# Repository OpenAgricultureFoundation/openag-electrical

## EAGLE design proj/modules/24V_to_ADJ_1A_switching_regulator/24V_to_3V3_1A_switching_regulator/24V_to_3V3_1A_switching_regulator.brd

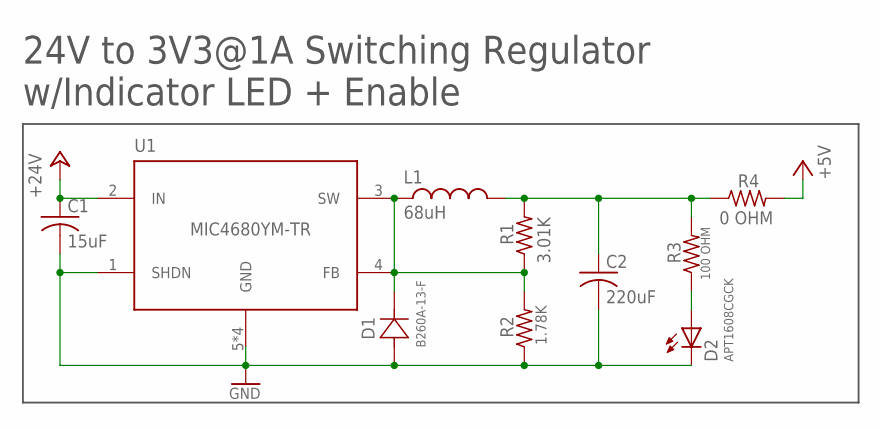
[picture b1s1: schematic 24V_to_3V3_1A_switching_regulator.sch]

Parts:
C1: 15uF; CT7343
C2: 220uF; CT7343
D1: B260A-13-F; SMA
D2: APT1608CGCK; CHIPLED_0603
L1: 68uH; UP2B
R1: 3.01K; RC0603N
R2: 1.78K; RC0603N
R3: 100 OHM; RC0603N
R4: 0 OHM; RC0603N
U1: MIC4680YM-TR; SOIC8

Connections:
+5V: R4.2
+24V: C1.+ (1(+)), U1.2 (IN)
GND: C1.- (2(-)), C2.- (2(-)), D1.2 (21), D2.C, R2.1, U1.1 (SHDN), U1.5 (GND), U1.6 (GND), U1.7 (GND), U1.8 (GND)
unnamed: D2.A, R3.1
unnamed: C2.+ (1(+)), L1.2, R1.2, R3.2, R4.1
unnamed: D1.1 (12), L1.1, R1.1, R2.2, U1.3 (SW), U1.4 (FB)

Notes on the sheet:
24V to 3V3@1A Switching Regulator w/Indicator LED + Enable

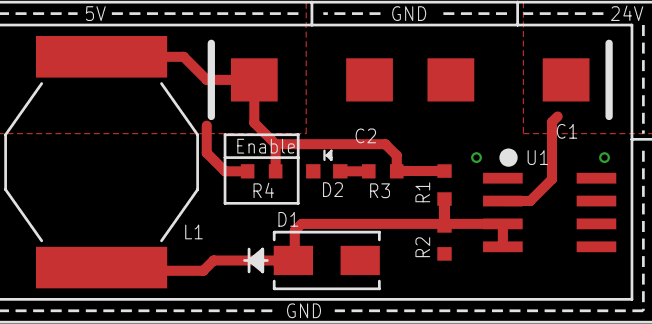
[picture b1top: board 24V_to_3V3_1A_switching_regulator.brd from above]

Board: 2 copper layers, 10 parts (0 on the bottom side), 5 nets.

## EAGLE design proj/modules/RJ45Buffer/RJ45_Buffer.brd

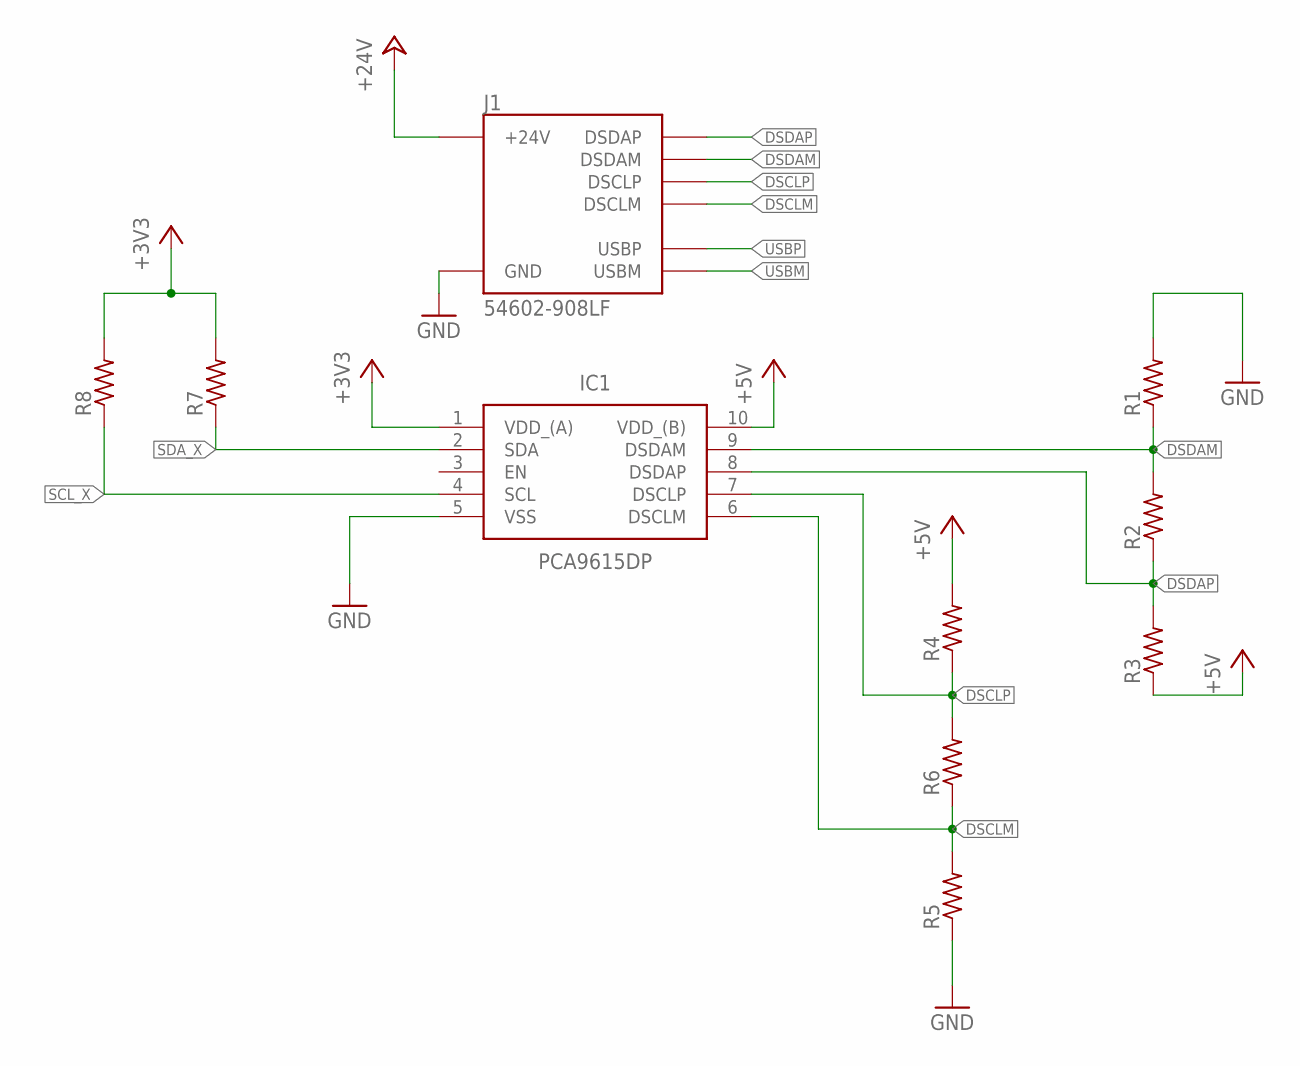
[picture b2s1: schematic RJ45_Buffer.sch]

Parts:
IC1: PCA9615DP; SOP50P490X110-10N
J1: 54602-908LF; OPENAG-V1-RJ45
R1, R2, R3, R4, R5, R6, R7, R8: R-US_R0603; R0603

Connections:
+3V3: IC1.1 (VDD_(A)), R7.2, R8.2
+5V: IC1.10 (VDD_(B)), R3.1, R4.2
+24V: J1.24V(6) (+24V)
DSCLM: IC1.6 (DSCLM), J1.DSCLM(5) (DSCLM), R5.2, R6.1
DSCLP: IC1.7 (DSCLP), J1.DSCLP(4) (DSCLP), R4.1, R6.2
DSDAM: IC1.9 (DSDAM), J1.DSDAM(2) (DSDAM), R1.1, R2.2
DSDAP: IC1.8 (DSDAP), J1.DSDAP(1) (DSDAP), R2.1, R3.2
GND: IC1.5 (VSS), J1.GND(3) (GND), R1.2, R5.1
SCL_X: IC1.4 (SCL), R8.1
SDA_X: IC1.2 (SDA), R7.1
USBM: J1.USBM(8) (USBM)
USBP: J1.USBP(7) (USBP)

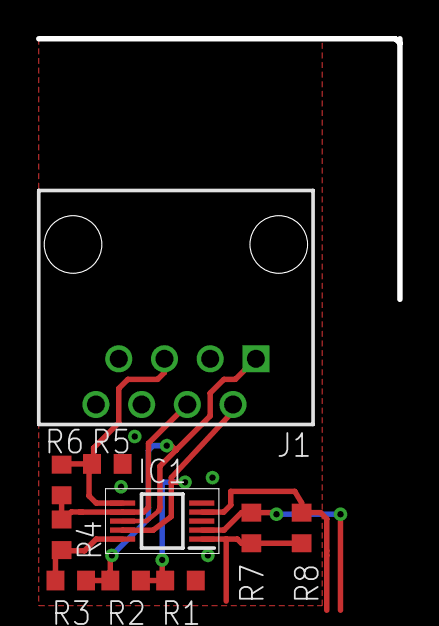
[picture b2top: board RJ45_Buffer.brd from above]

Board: 2 copper layers, 10 parts (0 on the bottom side), 9 nets.

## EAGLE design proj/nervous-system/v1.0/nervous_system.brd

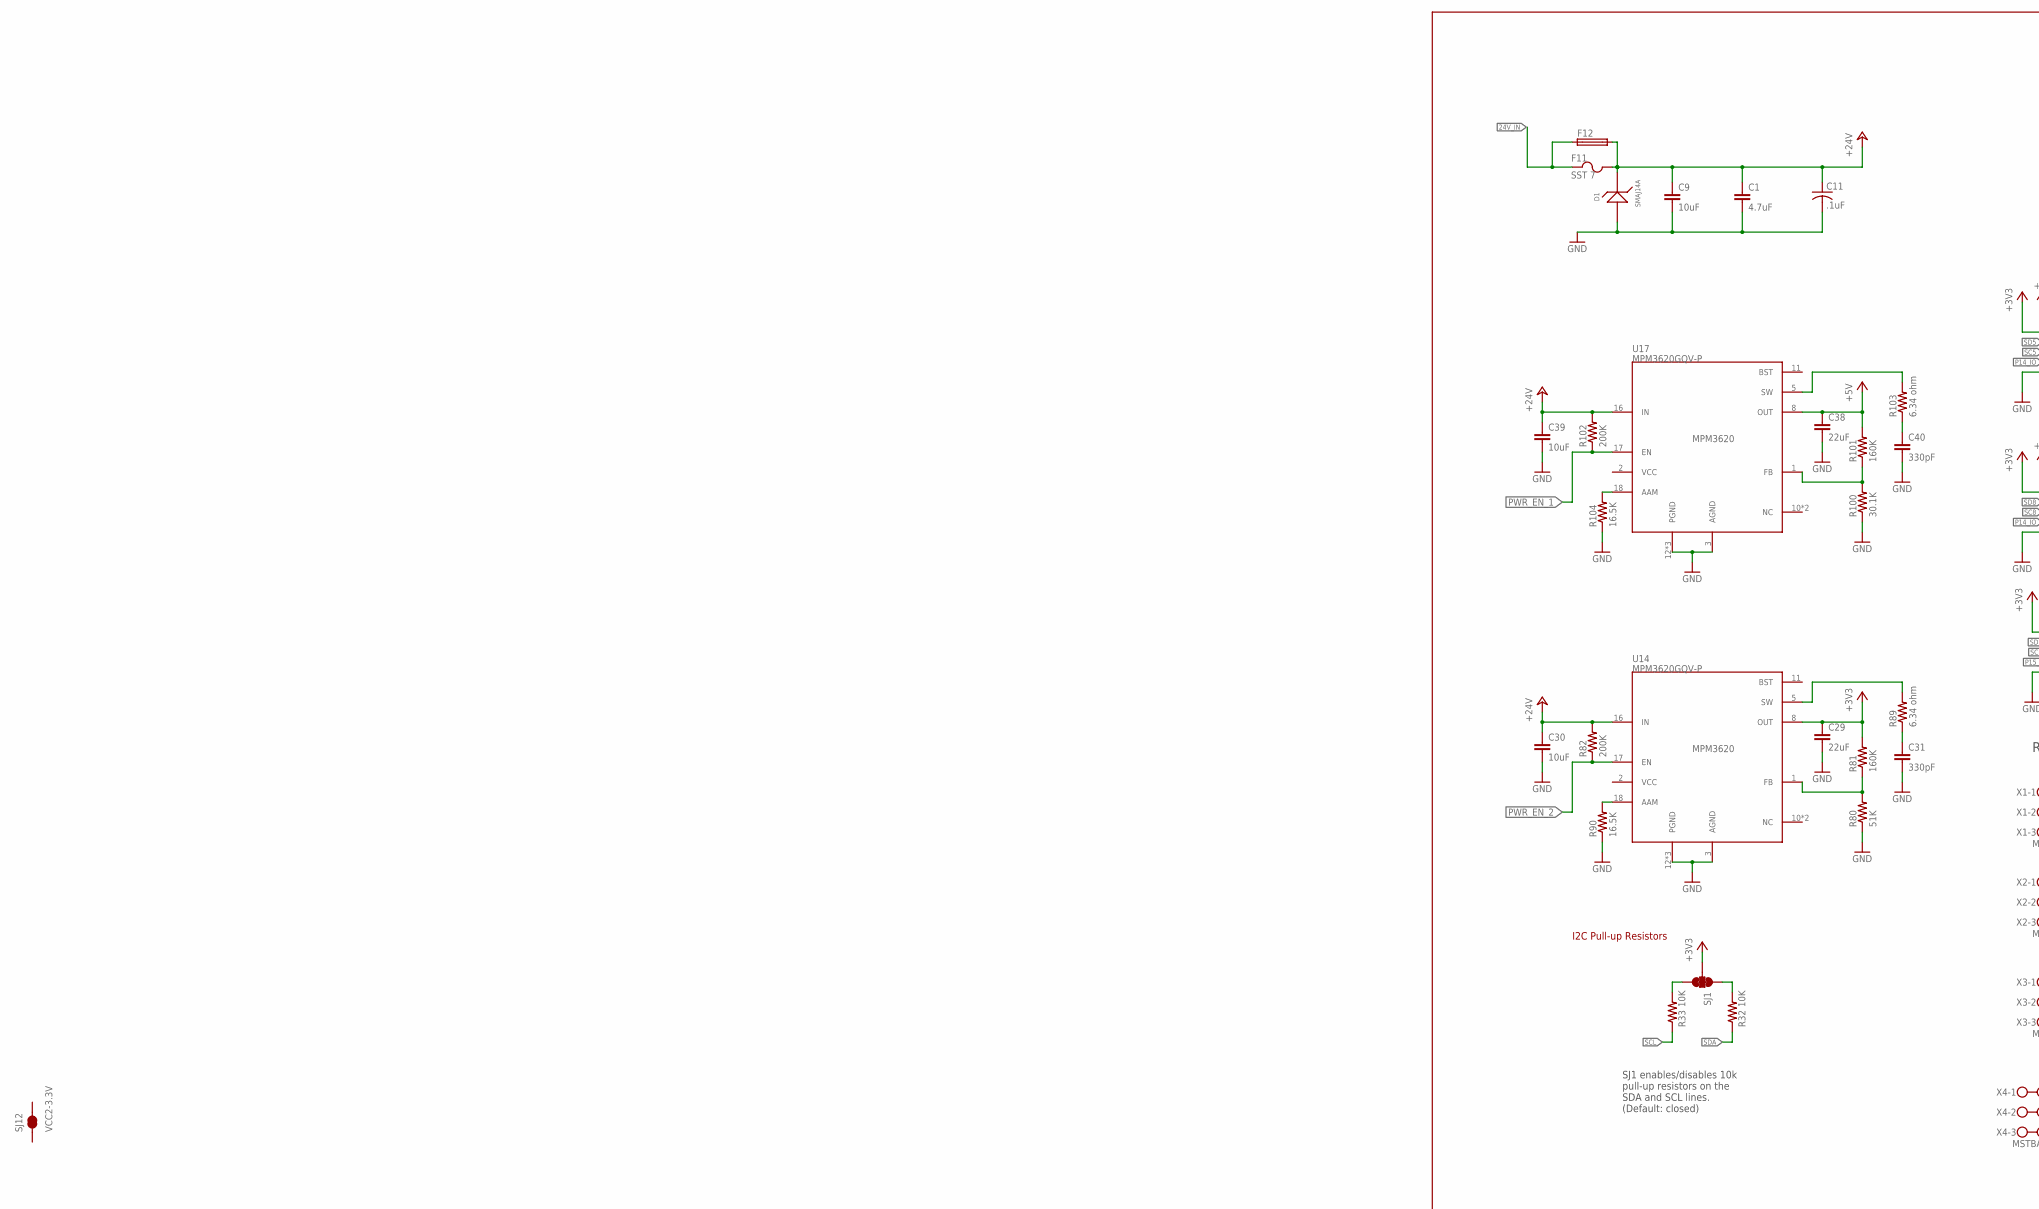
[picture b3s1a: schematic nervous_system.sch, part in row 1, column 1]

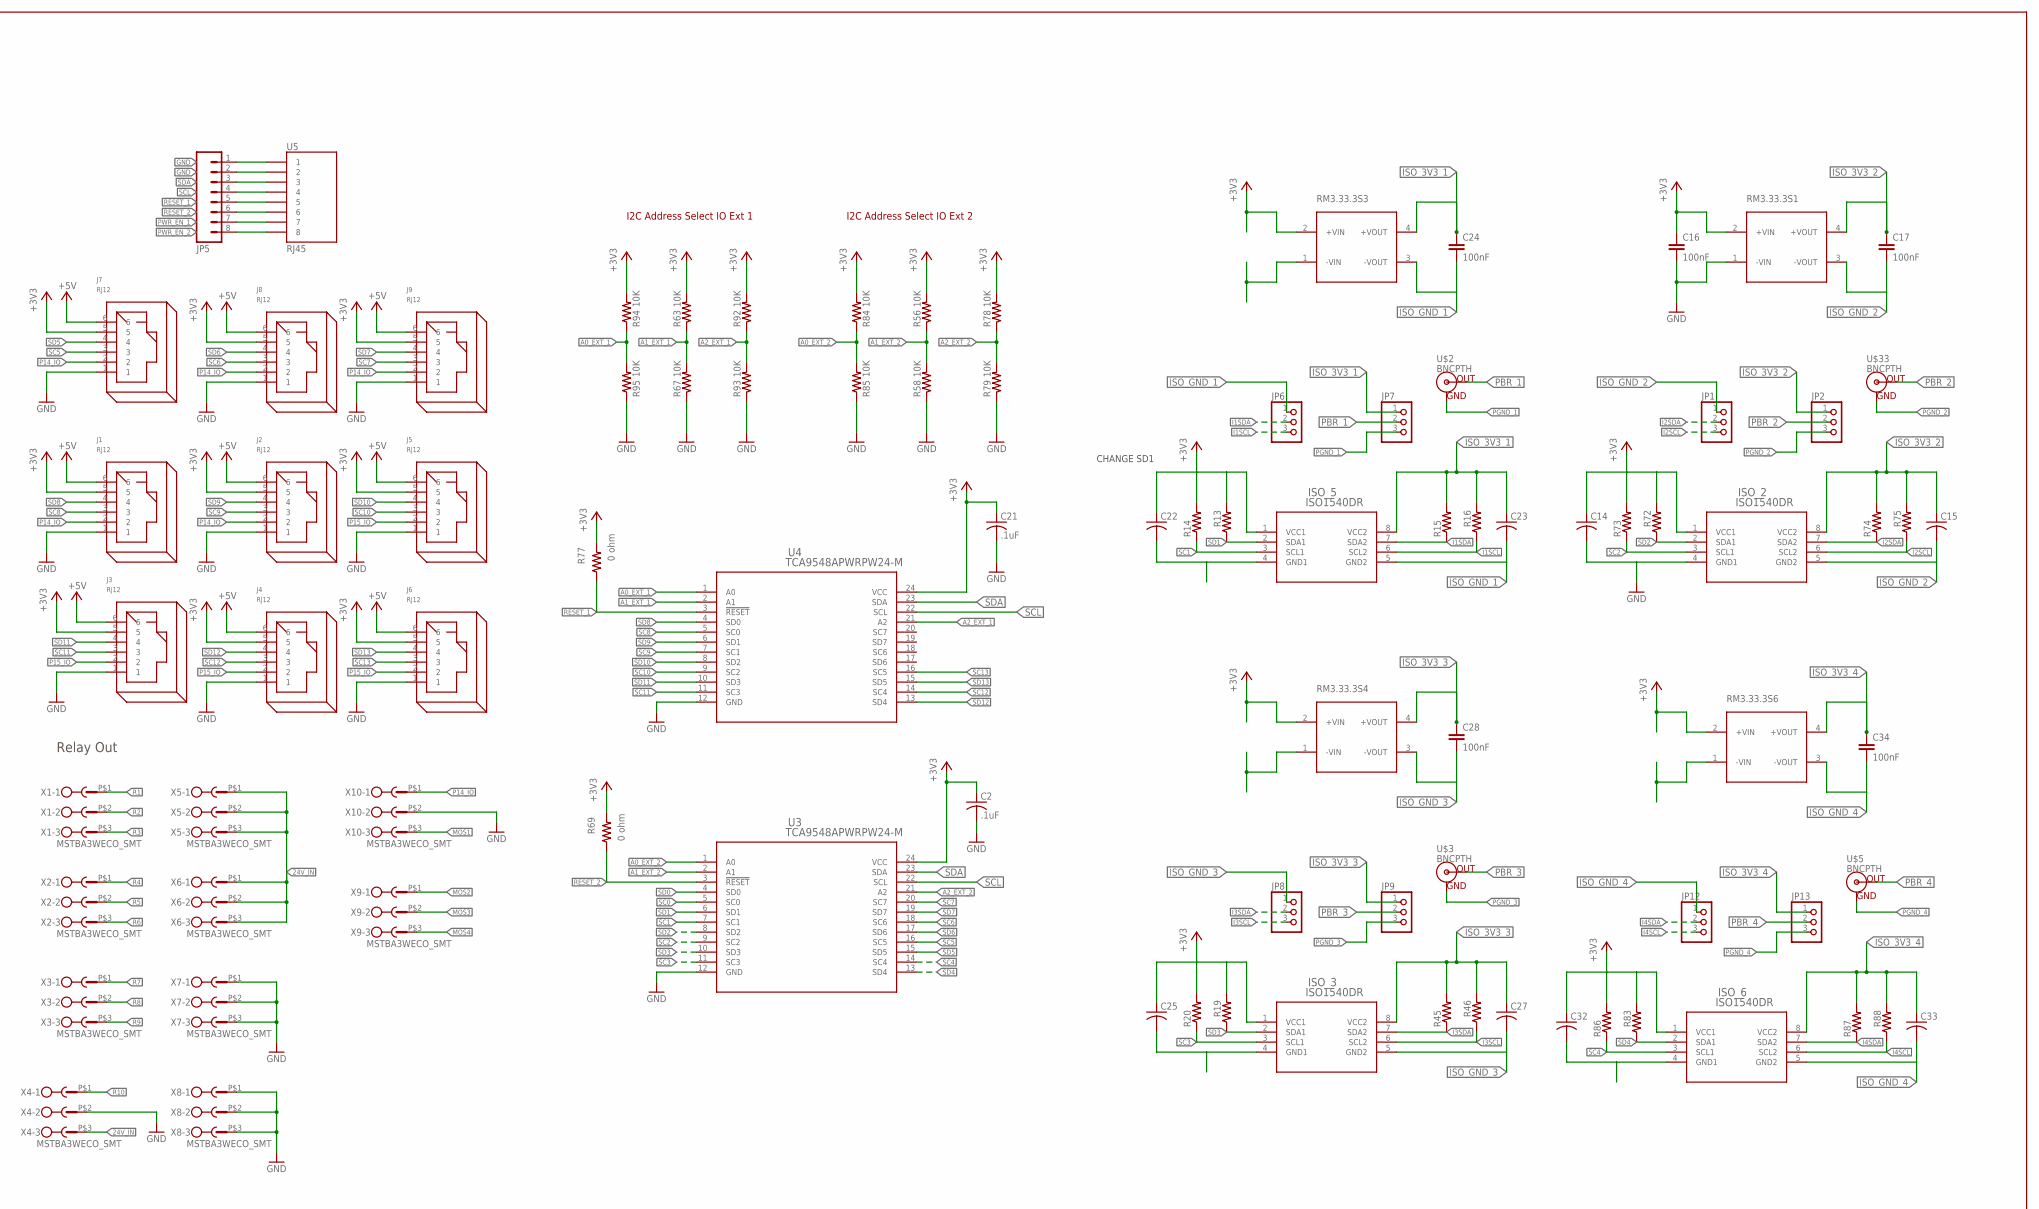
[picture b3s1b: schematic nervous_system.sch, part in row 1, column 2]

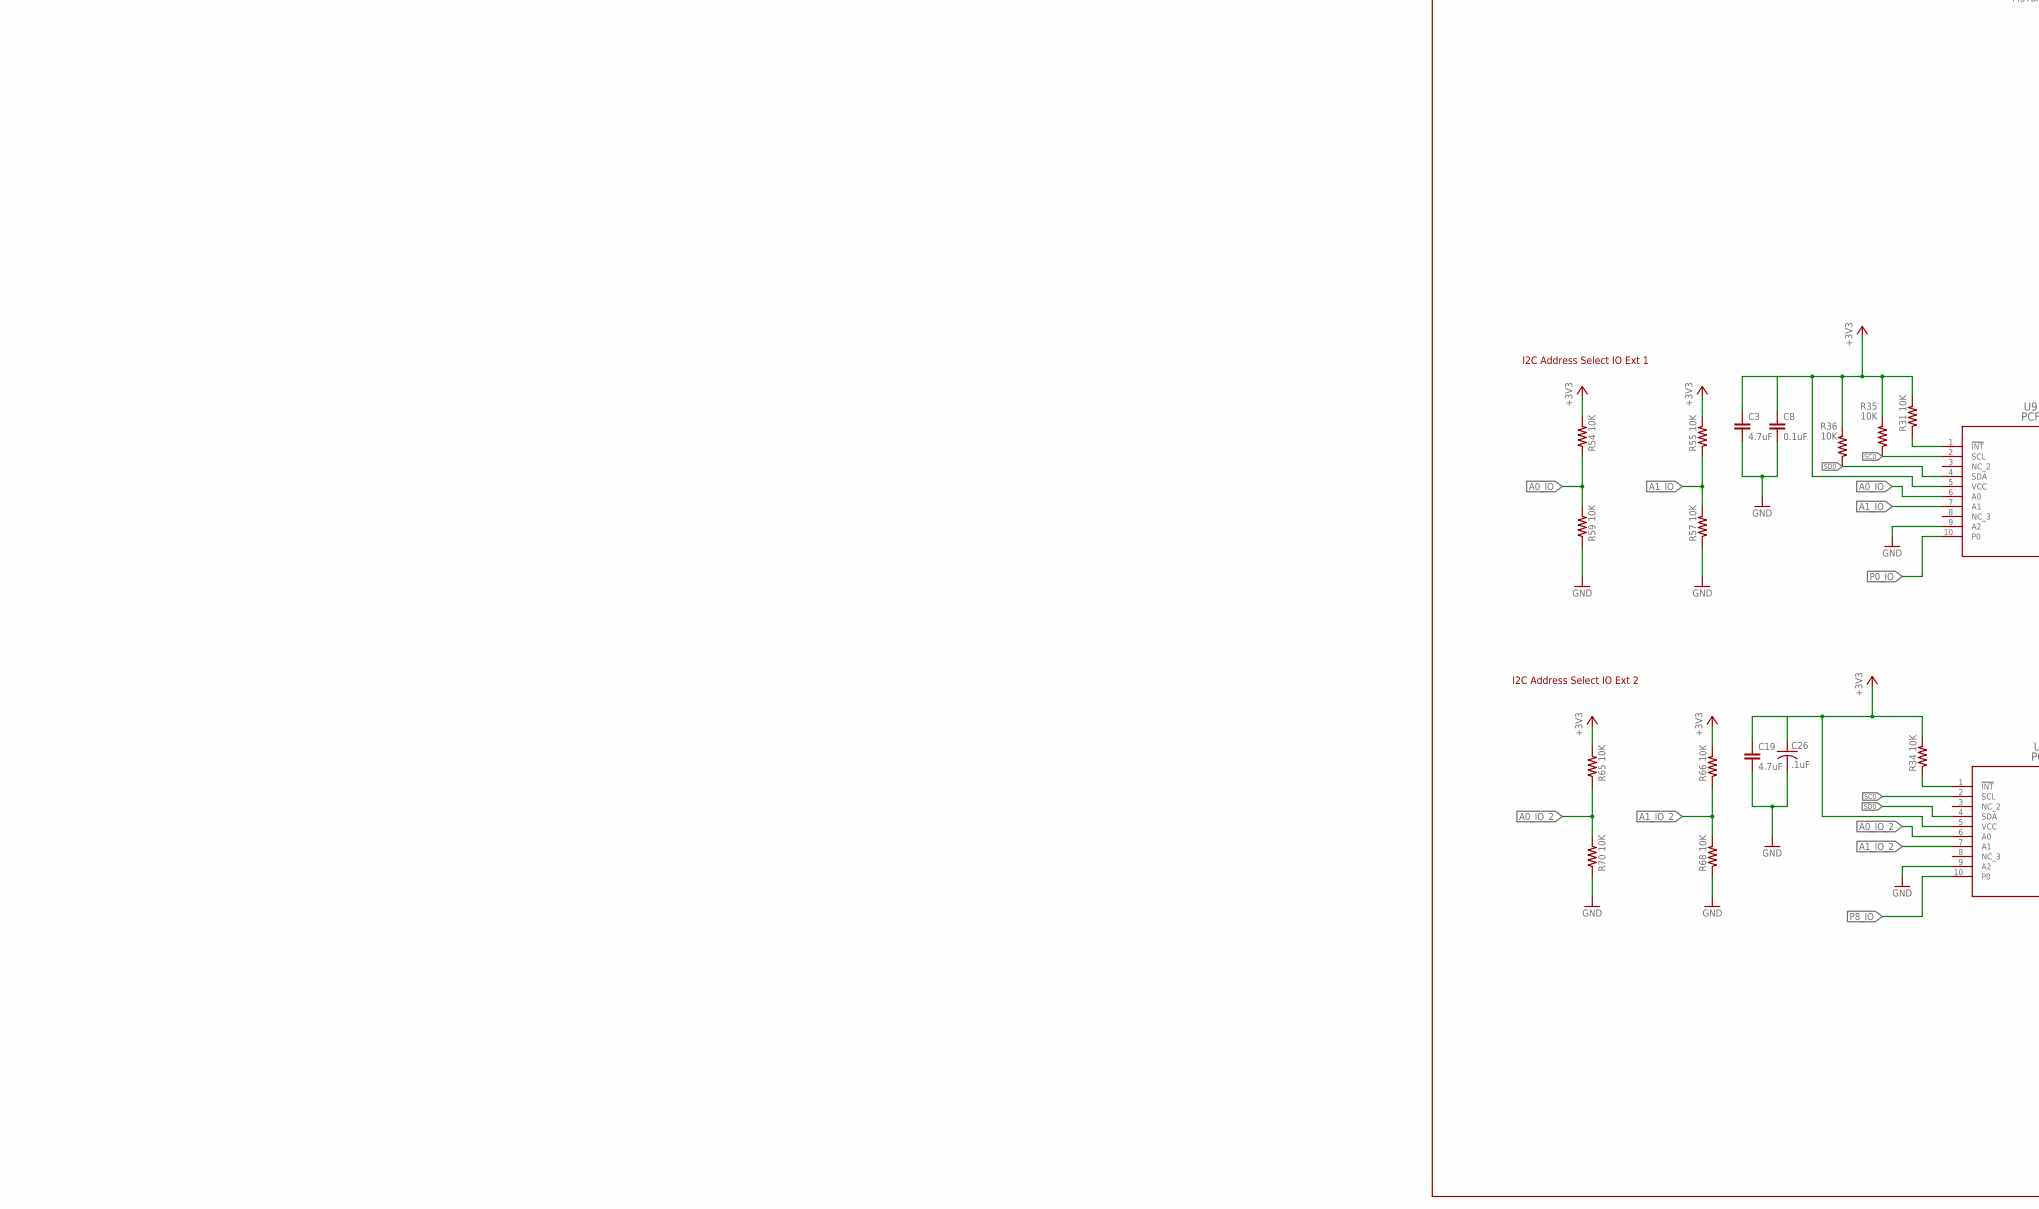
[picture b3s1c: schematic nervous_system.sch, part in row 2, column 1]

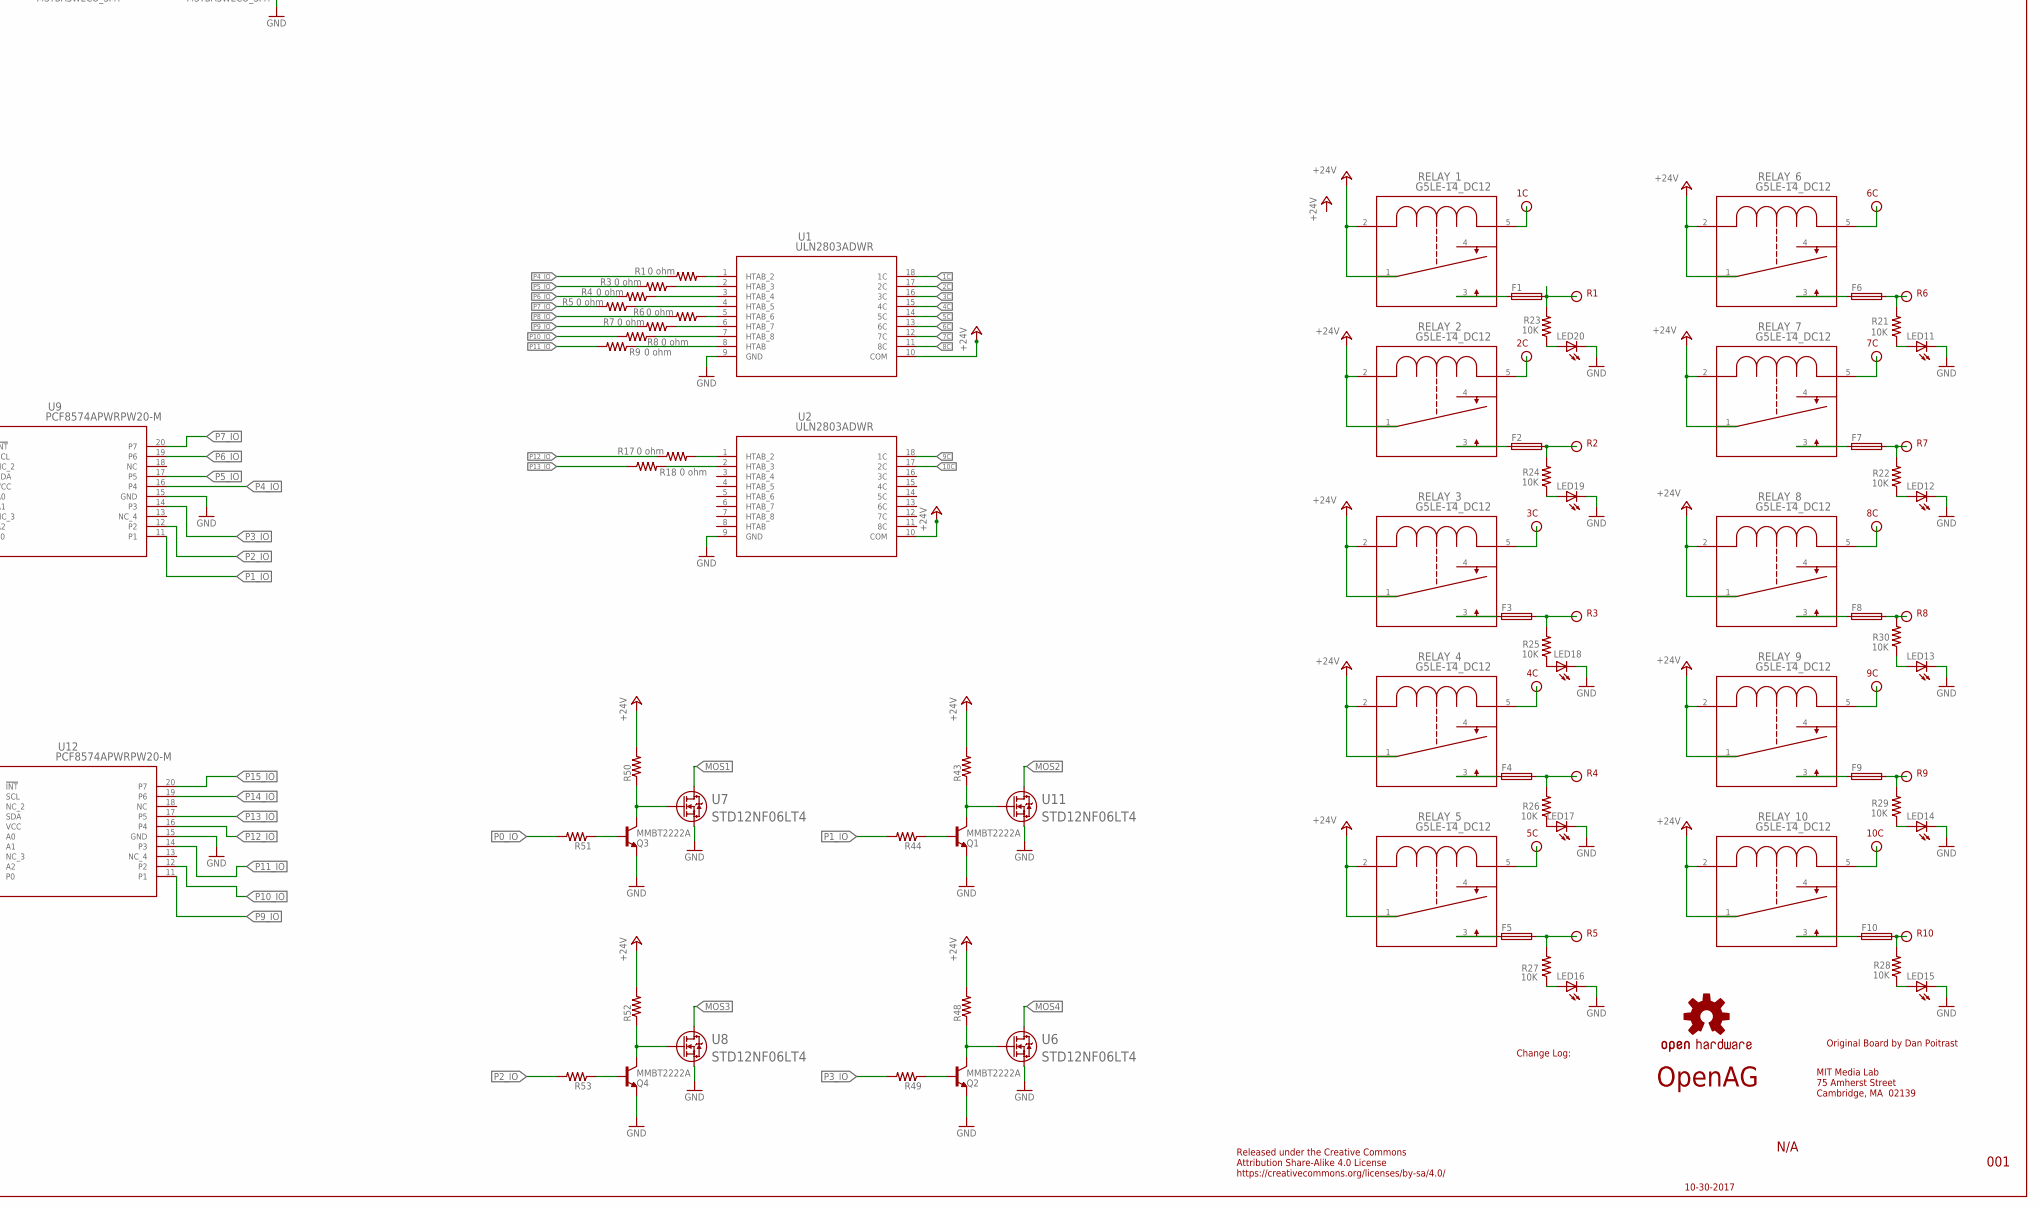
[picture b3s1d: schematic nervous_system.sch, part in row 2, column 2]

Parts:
C1, C3, C19: 4.7uF; CAP_C1206
C2, C11, C21, C26: .1uF; C0603@1
C8: 0.1uF; C1206C
C9, C30, C39: 10uF; C1206
C14, C15, C22, C23, C25, C27, C32, C33: C-USC0603; C0603@1
C16, C17, C24, C28, C34: 100nF; 0805@1
C29, C38: 22uF; C1206
C31, C40: 330pF; C0603
D1: SMAJ14A; DO-214AC
F1, F2, F3, F4, F5, F6, F7, F8, F9, F10, F12: GSH15
F11: SST 7; SS
ISO_2, ISO_3, ISO_5, ISO_6: ISO1540DR; D8
J1, J2, J3, J4, J5, J6, J7, J8, J9: RJ12
JP1, JP2, JP6, JP7, JP8, JP9, JP12, JP13: PINHD-1X3; 1X03
JP5: M08; 1X08
LED11, LED12, LED13, LED14, LED15, LED16, LED17, LED18, LED19, LED20: LED; SMARTLED-TTW
LOGO3: OSHW-LOGOS; OSHW-LOGO-S
Q1, Q2, Q3, Q4: MMBT2222A; SOT23-BEC
R1, R3, R4, R5, R6, R7, R8, R9, R17, R18, R69, R77: 0 ohm; R0603
R13, R14, R15, R16, R19, R20, R45, R46, R72, R73, R74, R75, R83, R86, R87, R88: R-US_R0603; R0603
R21, R22, R23, R24, R25, R26, R27, R28, R29, R30: 10K; R0603
R31, R32, R33, R34, R35, R36, R54, R55, R56, R57, R58, R59, R63, R65, R66, R67, R68, R70, R78, R79, R84, R85, R92, R93, R94, R95: 10K; 0603-RES
R43, R44, R48, R49, R50, R51, R52, R53: R-US_R0805W; R0805W
R80: 51K; RC0603N
R81, R101: 160K; RC0603N
R82, R102: 200K; RC0603N
R89, R103: 6.34 ohm; R0805
R90, R104: 16.5K; RC0603N
R100: 30.1K; RC0603N
RELAY_1, RELAY_2, RELAY_3, RELAY_4, RELAY_5, RELAY_6, RELAY_7, RELAY_8, RELAY_9, RELAY_10: G5LE-14_DC12; RELAY_G5LE-1
RM3.33.3S1, RM3.33.3S3, RM3.33.3S4, RM3.33.3S6: ROE-0505S; SIP4
SJ1: JUMPER-PAD-3-NC_BY_TRACE; PAD-JUMPER-3-3OF3_NC_BY_TRACE_YES_SILK_FULL_BOX
SJ12: VCC2-3.3V; PAD-JUMPER-2-NC_BY_TRACE_YES_SILK
U1, U2: ULN2803ADWR; DW18
U3, U4: TCA9548APWRPW24-M; PW24-M
U5: RJ45; RJ45-8
U6, U7, U8, U11: STD12NF06LT4; DPAK
U9, U12: PCF8574APWRPW20-M; PW20-M
U14, U17: MPM3620GQV-P; 20-POWERLFQFN-MODULE
U$2, U$3, U$5, U$33: BNCPTH; BNC
X1, X2, X3, X4, X5, X6, X7, X8, X9, X10: MSTBA3WECO_SMT; WECO_3POS_SMT

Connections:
1C: RELAY_1.5, U1.18 (1C)
2C: RELAY_2.5, U1.17 (2C)
3C: RELAY_3.5, U1.16 (3C)
4C: RELAY_4.5, U1.15 (4C)
5C: RELAY_5.5, U1.14 (5C)
6C: RELAY_6.5, U1.13 (6C)
7C: RELAY_7.5, U1.12 (7C)
8C: RELAY_8.5, U1.11 (8C)
9C: RELAY_9.5, U2.18 (1C)
10C: RELAY_10.5, U2.17 (2C)
24V_IN: F11.1, F12.1, X4.P$3, X5.P$1, X5.P$2, X5.P$3, X6.P$1, X6.P$2, X6.P$3
+3V3: C2.1, C3.1, C8.1, C14.1, C16.1, C19.1, C21.1, C22.1, C25.1, C26.1, C29.1, C32.1, ISO_2.1 (VCC1), ISO_3.1 (VCC1), ISO_5.1 (VCC1), ISO_6.1 (VCC1), J1.5, J2.5, J3.5, J4.5, J5.5, J6.5, J7.5, J8.5, J9.5, R13.2, R14.2, R19.2, R20.2, R31.2, R34.2, R35.2, R36.2, R54.2, R55.2, R56.2, R63.2, R65.2, R66.2, R69.2, R72.2, R73.2, R77.2, R78.2, R81.2, R83.2, R84.2, R86.2, R92.2, R94.2, RM3.33.3S1.2 (+VIN), RM3.33.3S3.2 (+VIN), RM3.33.3S4.2 (+VIN), RM3.33.3S6.2 (+VIN), SJ1.2, U3.24 (VCC), U4.24 (VCC), U9.5 (VCC), U12.5 (VCC), U14.8 (OUT)
+5V: C38.1, J1.6, J2.6, J3.6, J4.6, J5.6, J6.6, J7.6, J8.6, J9.6, R101.2, U17.8 (OUT)
+24V: C1.1, C9.1, C11.1, C30.1, C39.1, D1.C, F11.2, F12.2, R43.2, R48.2, R50.2, R52.2, R82.2, R102.2, RELAY_1.1 (2), RELAY_1.2 (1), RELAY_2.1 (2), RELAY_2.2 (1), RELAY_3.1 (2), RELAY_3.2 (1), RELAY_4.1 (2), RELAY_4.2 (1), RELAY_5.1 (2), RELAY_5.2 (1), RELAY_6.1 (2), RELAY_6.2 (1), RELAY_7.1 (2), RELAY_7.2 (1), RELAY_8.1 (2), RELAY_8.2 (1), RELAY_9.1 (2), RELAY_9.2 (1), RELAY_10.1 (2), RELAY_10.2 (1), U1.10 (COM), U2.10 (COM), U14.16 (IN), U17.16 (IN)
A0_EXT_1: R94.1, R95.2, U4.1 (A0)
A0_EXT_2: R84.1, R85.2, U3.1 (A0)
A0_IO: R54.1, R59.2, U9.6 (A0)
A0_IO_2: R65.1, R70.2, U12.6 (A0)
A1_EXT_1: R63.1, R67.2, U4.2 (A1)
A1_EXT_2: R56.1, R58.2, U3.2 (A1)
A1_IO: R55.1, R57.2, U9.7 (A1)
A1_IO_2: R66.1, R68.2, U12.7 (A1)
A2_EXT_1: R92.1, R93.2, U4.21 (A2)
A2_EXT_2: R78.1, R79.2, U3.21 (A2)
GND: C1.2, C2.2, C3.2, C8.2, C9.2, C11.2, C14.2, C16.2, C19.2, C21.2, C22.2, C25.2, C26.2, C29.2, C30.2, C31.2, C32.2, C38.2, C39.2, C40.2, D1.A, ISO_2.4 (GND1), ISO_3.4 (GND1), ISO_5.4 (GND1), ISO_6.4 (GND1), J1.1, J2.1, J3.1, J4.1, J5.1, J6.1, J7.1, J8.1, J9.1, JP5.1, JP5.2, LED11.C@1 (C), LED12.C@1 (C), LED13.C@1 (C), LED14.C@1 (C), LED15.C@1 (C), LED16.C@1 (C), LED17.C@1 (C), LED18.C@1 (C), LED19.C@1 (C), LED20.C@1 (C), Q1.E, Q2.E, Q3.E, Q4.E, R57.1, R58.1, R59.1, R67.1, R68.1, R70.1, R79.1, R80.1, R85.1, R90.1, R93.1, R95.1, R100.1, R104.1, RM3.33.3S1.1 (-VIN), RM3.33.3S3.1 (-VIN), RM3.33.3S4.1 (-VIN), RM3.33.3S6.1 (-VIN), U1.9 (GND), U2.9 (GND), U3.12 (GND), U4.12 (GND), U5.1, U5.2, U6.2 (3), U7.2 (3), U8.2 (3), U9.9 (A2), U9.15 (GND), U11.2 (3), U12.9 (A2), U12.15 (GND), U14.3 (AGND), U14.12 (PGND), U14.13 (PGND), U14.14 (PGND), U17.3 (AGND), U17.12 (PGND), U17.13 (PGND), U17.14 (PGND), X4.P$2, X7.P$1, X7.P$2, X7.P$3, X8.P$1, X8.P$2, X8.P$3, X10.P$2
HTAB: U2.8 (HTAB)
HTAB_4: U2.3 (HTAB_4)
HTAB_5: U2.4 (HTAB_5)
HTAB_6: U2.5 (HTAB_6)
HTAB_7: U2.6 (HTAB_7)
HTAB_8: U2.7 (HTAB_8)
I1SCL: ISO_5.6 (SCL2), JP6.3, R16.1
I1SDA: ISO_5.7 (SDA2), JP6.2, R15.1
I2SCL: ISO_2.6 (SCL2), JP1.3, R75.1
I2SDA: ISO_2.7 (SDA2), JP1.2, R74.1
I3SCL: ISO_3.6 (SCL2), JP8.3, R46.1
I3SDA: ISO_3.7 (SDA2), JP8.2, R45.1
I4SCL: ISO_6.6 (SCL2), JP12.3, R88.1
I4SDA: ISO_6.7 (SDA2), JP12.2, R87.1
ISO_3V3_1: C23.1, C24.1, ISO_5.8 (VCC2), JP7.1, R15.2, R16.2, RM3.33.3S3.4 (+VOUT)
ISO_3V3_2: C15.1, C17.1, ISO_2.8 (VCC2), JP2.1, R74.2, R75.2, RM3.33.3S1.4 (+VOUT)
ISO_3V3_3: C27.1, C28.1, ISO_3.8 (VCC2), JP9.1, R45.2, R46.2, RM3.33.3S4.4 (+VOUT)
ISO_3V3_4: C33.1, C34.1, ISO_6.8 (VCC2), JP13.1, R87.2, R88.2, RM3.33.3S6.4 (+VOUT)
ISO_GND_1: C23.2, C24.2, ISO_5.5 (GND2), JP6.1, RM3.33.3S3.3 (-VOUT)
ISO_GND_2: C15.2, C17.2, ISO_2.5 (GND2), JP1.1, RM3.33.3S1.3 (-VOUT)
ISO_GND_3: C27.2, C28.2, ISO_3.5 (GND2), JP8.1, RM3.33.3S4.3 (-VOUT)
ISO_GND_4: C33.2, C34.2, ISO_6.5 (GND2), JP12.1, RM3.33.3S6.3 (-VOUT)
MOS1: U7.3 (2), X10.P$3
MOS2: U11.3 (2), X9.P$1
MOS3: U8.3 (2), X9.P$2
MOS4: U6.3 (2), X9.P$3
unnamed: R1.2, U1.1 (HTAB_2)
unnamed: R3.1, U1.2 (HTAB_3)
unnamed: R4.1, U1.3 (HTAB_4)
unnamed: R5.1, U1.4 (HTAB_5)
unnamed: R6.1, U1.5 (HTAB_6)
unnamed: R7.1, U1.6 (HTAB_7)
unnamed: R8.1, U1.7 (HTAB_8)
unnamed: R9.1, U1.8 (HTAB)
unnamed: F10.1, RELAY_10.3
unnamed: F9.1, RELAY_9.3
unnamed: F8.1, RELAY_8.3
unnamed: F7.1, RELAY_7.3
unnamed: R80.2, R81.1, U14.1 (FB)
unnamed: R89.2, U14.5 (SW)
unnamed: C31.1, R89.1
unnamed: R90.2, U14.18 (AAM)
unnamed: F6.1, RELAY_6.3
unnamed: F1.1, RELAY_1.3
unnamed: F2.1, RELAY_2.3
unnamed: F3.1, RELAY_3.3
unnamed: F4.1, RELAY_4.3
unnamed: R100.2, R101.1, U17.1 (FB)
unnamed: F5.1, RELAY_5.3
unnamed: R103.2, U17.5 (SW)
unnamed: Q1.C, R43.1, U11.1
unnamed: Q1.B, R44.1
unnamed: C40.1, R103.1
unnamed: R104.2, U17.18 (AAM)
unnamed: Q2.C, R48.1, U6.1
unnamed: Q2.B, R49.1
unnamed: Q3.C, R50.1, U7.1
unnamed: Q3.B, R51.1
unnamed: R17.2, U2.1 (HTAB_2)
unnamed: R18.2, U2.2 (HTAB_3)
unnamed: R34.1, U12.1 (!INT)
unnamed: LED11.A@1 (A), R21.1
unnamed: LED12.A@1 (A), R22.1
unnamed: LED16.A@1 (A), R27.1
unnamed: LED17.A@1 (A), R26.1
unnamed: LED18.A@1 (A), R25.1
unnamed: LED20.A@1 (A), R23.1
unnamed: LED19.A@1 (A), R24.1
unnamed: LED13.A@1 (A), R30.1
unnamed: LED14.A@1 (A), R29.1
unnamed: LED15.A@1 (A), R28.1
unnamed: Q4.C, R52.1, U8.1
unnamed: Q4.B, R53.1
unnamed: R31.1, U9.1 (!INT)
unnamed: R33.2, SJ1.3
unnamed: R32.2, SJ1.1
P0_IO: R51.2, U9.10 (P0)
P1_IO: R44.2, U9.11 (P1)
P2_IO: R53.2, U9.12 (P2)
P3_IO: R49.2, U9.14 (P3)
P4_IO: R1.1, U9.16 (P4)
P5_IO: R3.2, U9.17 (P5)
P6_IO: R4.2, U9.19 (P6)
P7_IO: R5.2, U9.20 (P7)
P8_IO: R6.2, U12.10 (P0)
P9_IO: R7.2, U12.11 (P1)
P10_IO: R8.2, U12.12 (P2)
P11_IO: R9.2, U12.14 (P3)
P12_IO: R17.1, U12.16 (P4)
P13_IO: R18.1, U12.17 (P5)
P14_IO: J1.2, J2.2, J7.2, J8.2, J9.2, U12.19 (P6), X10.P$1
P15_IO: J3.2, J4.2, J5.2, J6.2, U12.20 (P7)
PBR_1: JP7.2, U$2.S (OUT)
PBR_2: JP2.2, U$33.S (OUT)
PBR_3: JP9.2, U$3.S (OUT)
PBR_4: JP13.2, U$5.S (OUT)
PGND_1: JP7.3, U$2.GND
PGND_2: JP2.3, U$33.GND
PGND_3: JP9.3, U$3.GND
PGND_4: JP13.3, U$5.GND
PWR_EN_1: JP5.7, R102.1, U5.7, U17.17 (EN)
PWR_EN_2: JP5.8, R82.1, U5.8, U14.17 (EN)
R1: F1.2, R23.2, X1.P$1
R2: F2.2, R24.2, X1.P$2
R3: F3.2, R25.2, X1.P$3
R4: F4.2, R26.2, X2.P$1
R5: F5.2, R27.2, X2.P$2
R6: F6.2, R21.2, X2.P$3
R7: F7.2, R22.2, X3.P$1
R8: F8.2, R30.2, X3.P$2
R9: F9.2, R29.2, X3.P$3
R10: F10.2, R28.2, X4.P$1
RESET_1: JP5.5, R77.1, U4.3 (!RESET), U5.5
RESET_2: JP5.6, R69.1, U3.3 (!RESET), U5.6
SC0: R35.1, U3.5 (SC0), U9.2 (SCL), U12.2 (SCL)
SC1: ISO_5.3 (SCL1), R14.1, U3.7 (SC1)
SC2: ISO_2.3 (SCL1), R73.1, U3.9 (SC2)
SC3: ISO_3.3 (SCL1), R20.1, U3.11 (SC3)
SC4: ISO_6.3 (SCL1), R86.1, U3.14 (SC4)
SC5: J7.3, U3.16 (SC5)
SC6: J8.3, U3.18 (SC6)
SC7: J9.3, U3.20 (SC7)
SC8: J1.3, U4.5 (SC0)
SC9: J2.3, U4.7 (SC1)
SC10: J5.3, U4.9 (SC2)
SC11: J3.3, U4.11 (SC3)
SC12: J4.3, U4.14 (SC4)
SC13: J6.3, U4.16 (SC5)
SCL: JP5.4, R33.1, U3.22 (SCL), U4.22 (SCL), U5.4
SD0: R36.1, U3.4 (SD0), U9.4 (SDA), U12.4 (SDA)
SD1: ISO_5.2 (SDA1), R13.1, U3.6 (SD1)
SD2: ISO_2.2 (SDA1), R72.1, U3.8 (SD2)
SD3: ISO_3.2 (SDA1), R19.1, U3.10 (SD3)
SD4: ISO_6.2 (SDA1), R83.1, U3.13 (SD4)
SD5: J7.4, U3.15 (SD5)
SD6: J8.4, U3.17 (SD6)
SD7: J9.4, U3.19 (SD7)
SD8: J1.4, U4.4 (SD0)
SD9: J2.4, U4.6 (SD1)
SD10: J5.4, U4.8 (SD2)
SD11: J3.4, U4.10 (SD3)
SD12: J4.4, U4.13 (SD4)
SD13: J6.4, U4.15 (SD5)
SDA: JP5.3, R32.1, U3.23 (SDA), U4.23 (SDA), U5.3

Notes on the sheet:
10C
10-30-2017
001
OpenAG
MIT Media Lab 75 Amherst Street Cambridge, MA 02139
Original Board by Dan Poitrast
Change Log:
N/A
Relay Out
R10
SJ1 enables/disables 10k pull-up resistors on the SDA and SCL lines. (Default: closed)
I2C Address Select IO Ext 1
I2C Pull-up Resistors
I2C Address Select IO Ext 2
CHANGE SD1
Released under the Creative Commons Attribution Share-Alike 4.0 License https://creativecommons.org/licenses/by-sa/4.0/

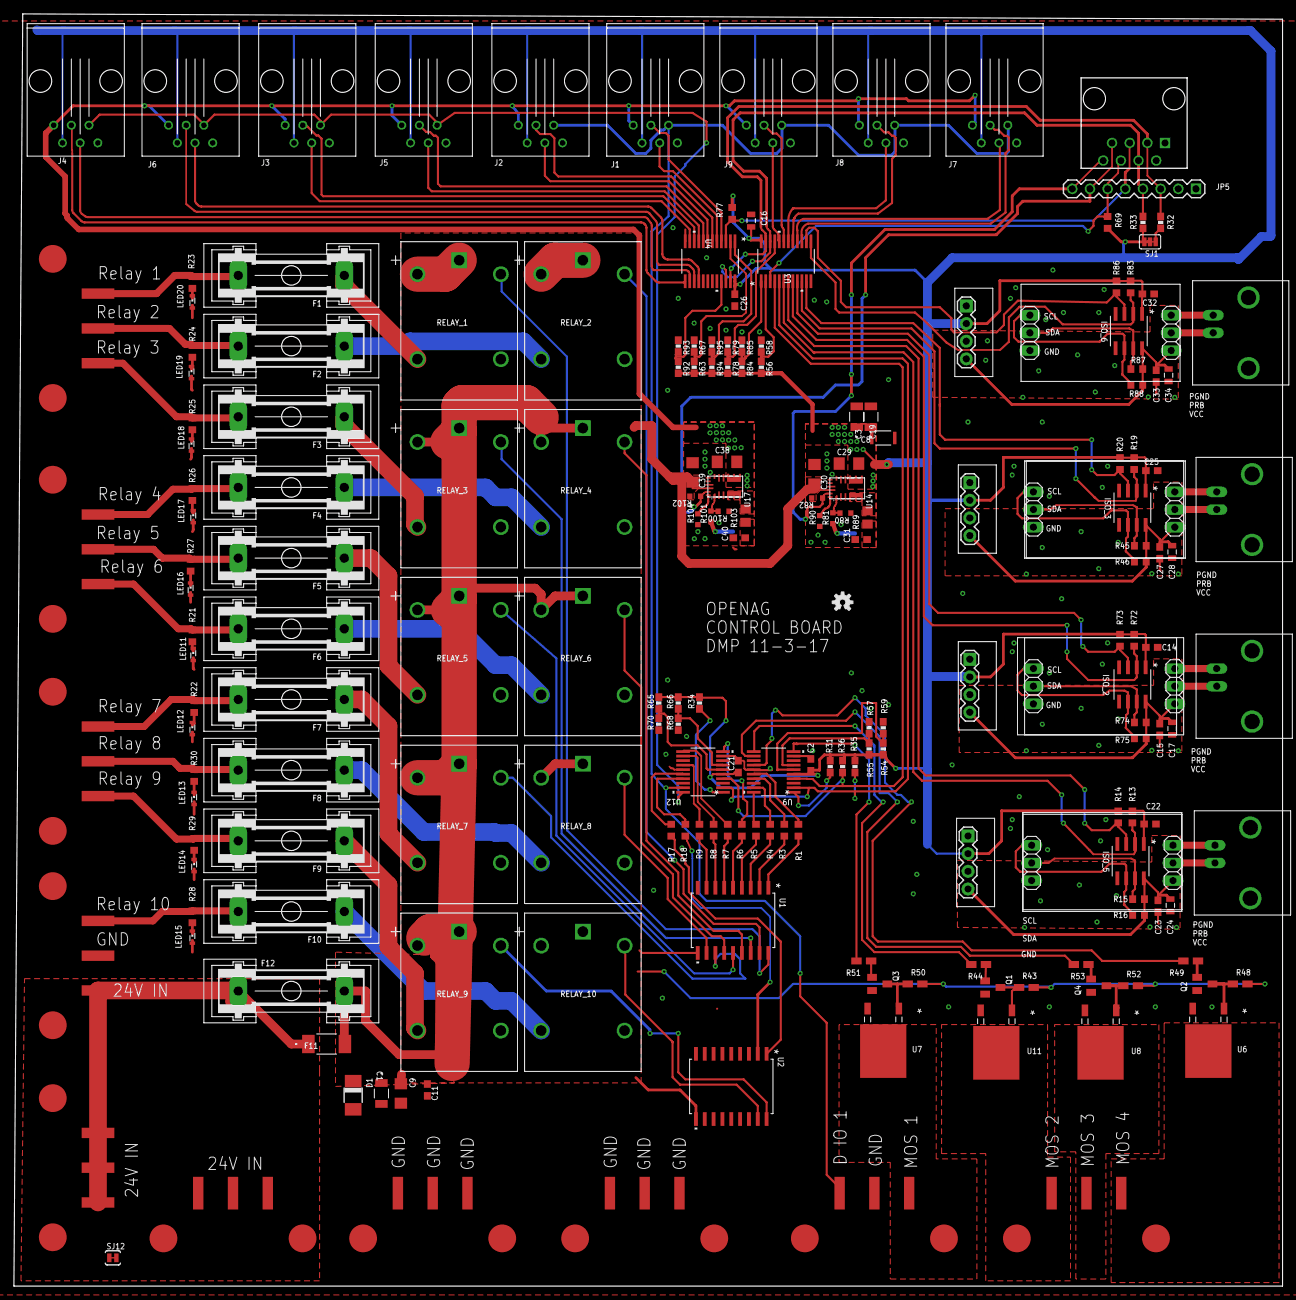
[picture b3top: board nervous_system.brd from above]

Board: 2 copper layers, 182.4 x 182.9 mm, 203 parts (0 on the bottom side), 163 nets.

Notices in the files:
parts and their libraries:
SparkFun-Aesthetics: Licensing: CC v3.0 Share-Alike You are welcome to use this library for commercial purposes.
SparkFun-Capacitors: Licensing: Creative Commons ShareAlike 4.0 International - https://creativecommons.org/licenses/by-sa/4.0
